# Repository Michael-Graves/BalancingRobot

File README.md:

# BalancingRobot
Repo for a balancing robot based on the TIVA C processor and Pololu's Micro Metal Gearmotors/encoders

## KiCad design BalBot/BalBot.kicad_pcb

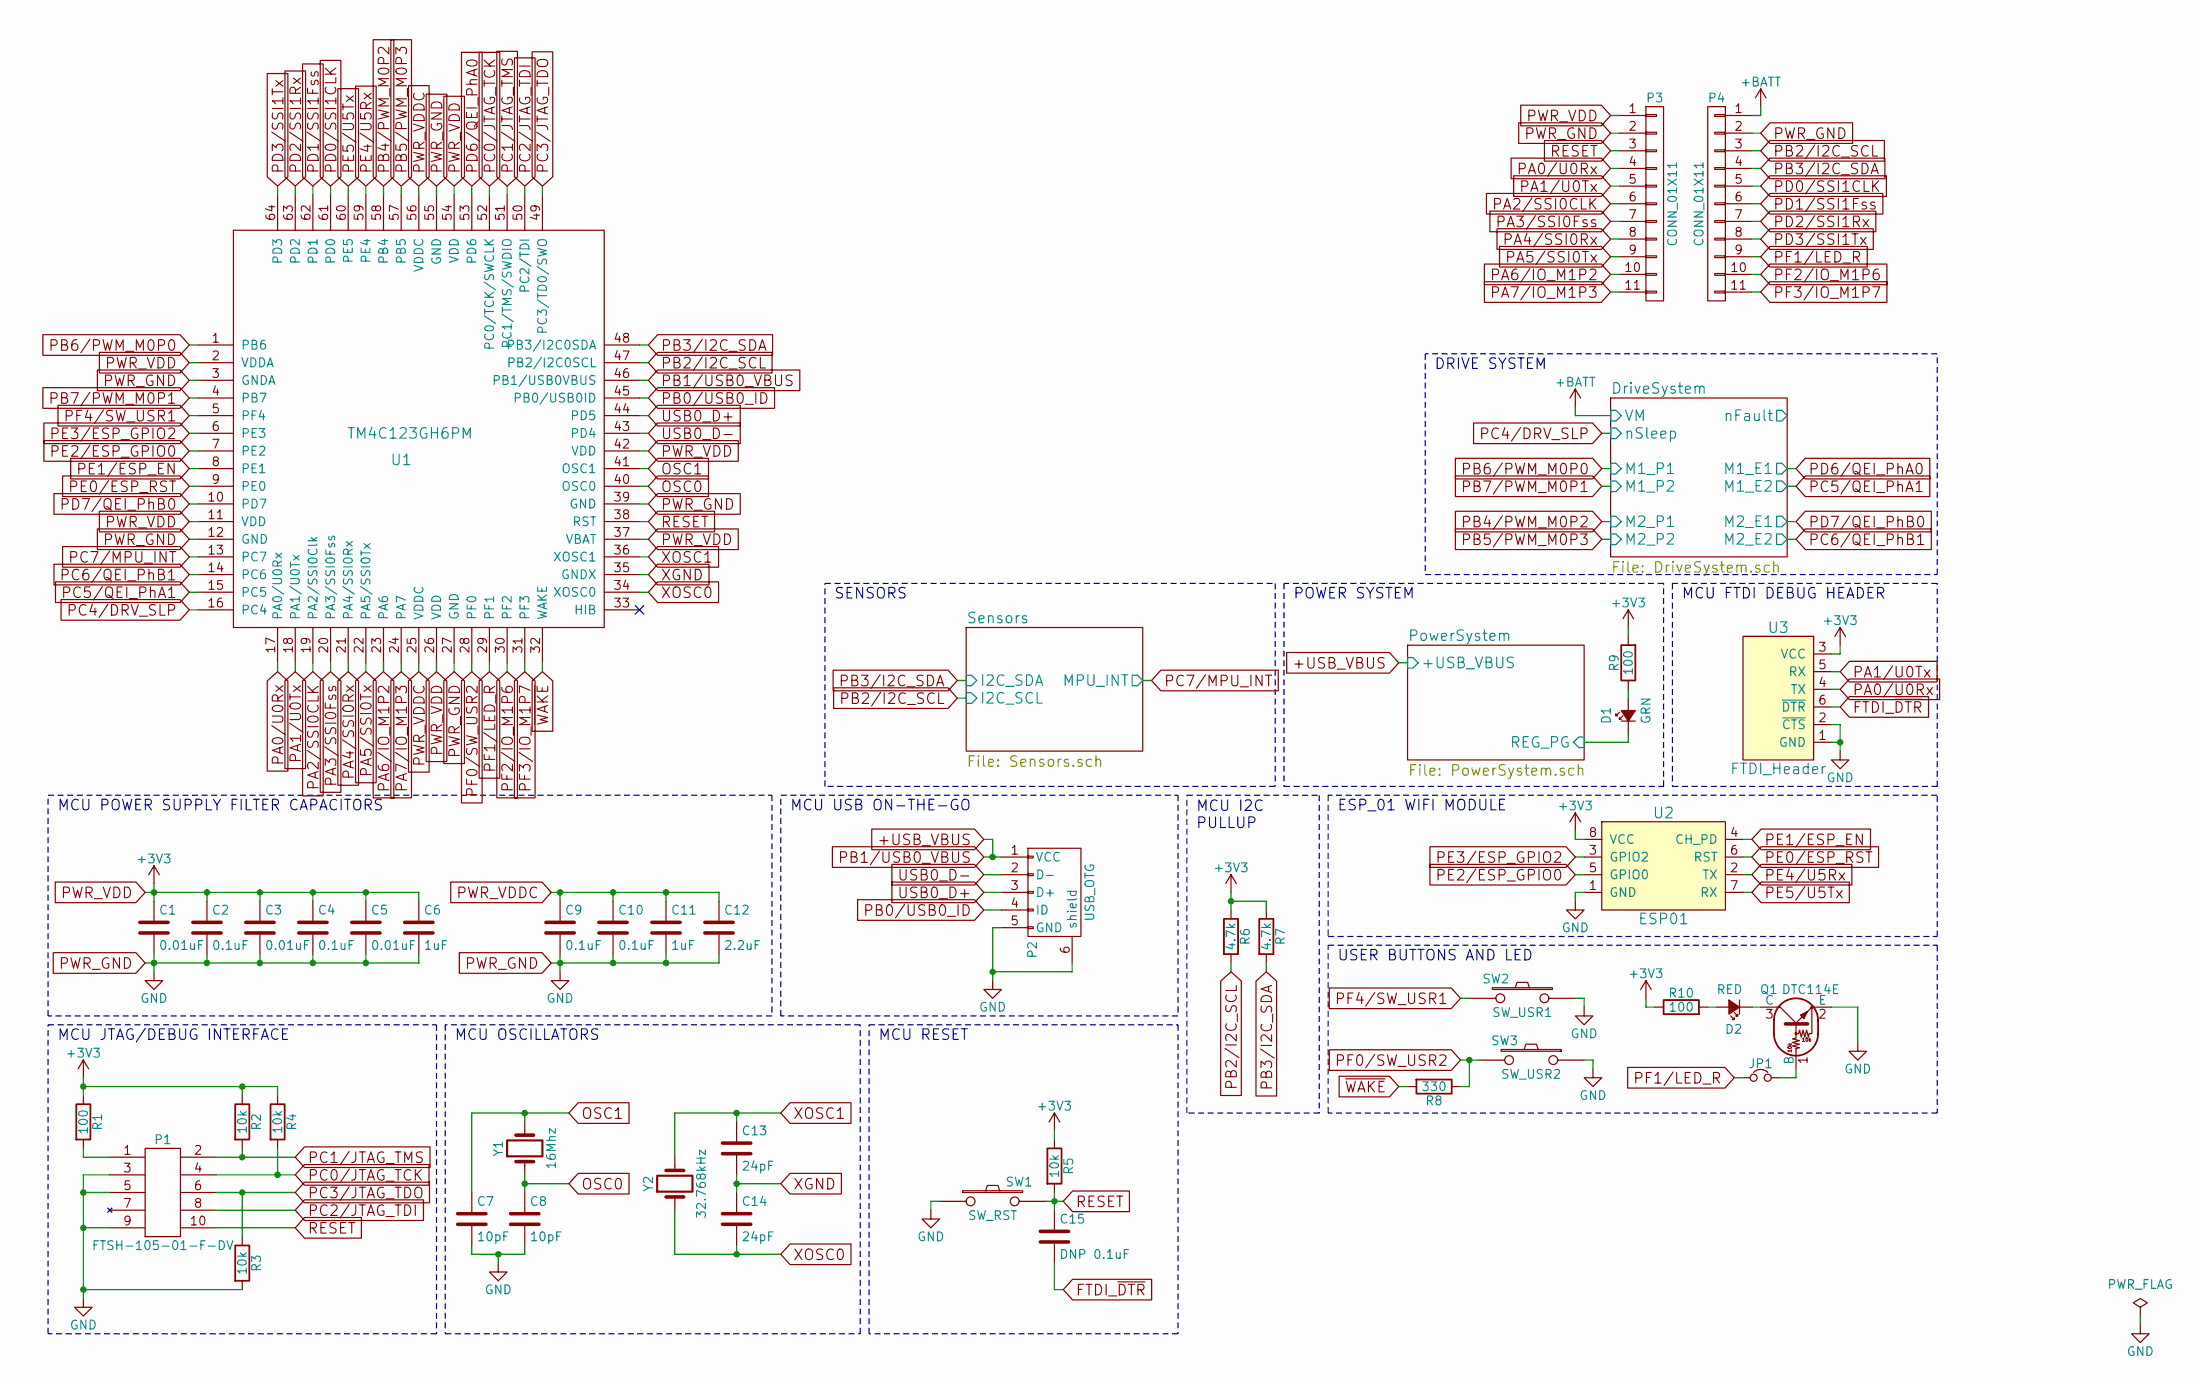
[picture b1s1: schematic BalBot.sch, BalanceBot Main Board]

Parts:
C1, C3, C5: 0.01uF; C_0402; DigiKey 490-6339-1-ND
C2, C4, C9, C10: 0.1uF; C_0402; DigiKey 490-9997-1-ND
C6, C11: 1uF; C_0402; DigiKey 490-12237-1-ND
C7, C8: 10pF; C_0402; DigiKey 490-14348-1-ND
C12: 2.2uF; C_0603; Digikey 490-3296-1-ND
C13, C14: 24pF; C_0402; DigiKey 490-17445-1-ND
C15: DNP 0.1uF; C_0402; DigiKey 490-9997-1-ND
D1: GRN; LED_0805
D2: RED; LED_0805
JP1: Jumper_NC_Small; Jumper_NC
P1: FTSH-105-01-F-DV; Pin_Header_Straight_2x05_Pitch1.00mm_SMD
P2: USB_OTG; USB_Micro-B; DigiKey 609-4618-1-ND
P3, P4: CONN_01X11; Pin_Header_Straight_1x11_Pitch2.54mm
Q1: DTC114E; SOT-416; DigiKey DTC114EET1GOSCT-ND
R1, R9, R10: 100; R_0805; DigiKey 311-100CRCT-ND
R2, R3, R4, R5: 10k; R_0805; DigiKey 311-10.0KCRCT-ND
R6, R7: 4.7k; R_0805; DigiKey 311-4.70KCRCT-ND
R8: 330; R_0805; DigiKey 311-330CRCT-ND
SW1: SW_RST; SW_SPST_6x6mm; DigiKey CKN9112CT-ND
SW2: SW_USR1; SW_SPST_6x6mm; DigiKey CKN9112CT-ND
SW3: SW_USR2; SW_SPST_6x6mm; DigiKey CKN9112CT-ND
U1: TM4C123GH6PM; LQFP-64_10x10mm_Pitch0.5mm
U2: ESP01; Pin_Header_Straight_2x04_Pitch2.54mm
U3: FTDI_Header; Pin_Header_Straight_1x06_Pitch2.54mm
Y1: 16Mhz; Crystal_SMD_5032-2pin_5.0x3.2mm; DigiKey 644-1037-1-ND
Y2: 32.768kHz; Crystal_32768Hz_Radial_Can; DigiKey 535-9033-1-ND

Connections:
+USB_VBUS: P2.1 (VCC), U1.46 (PB1/USB0VBUS); also elsewhere on the board
/PowerSystem/REG_PG: D1.1 (K); also elsewhere on the board
FTDI_~DTR: C15.2, U3.6 (~DTR)
unnamed: D1.2 (A), R9.1
unnamed: D2.1 (K), Q1.3 (C)
unnamed: D2.2 (A), R10.2
unnamed: JP1.2, Q1.1 (B)
unnamed: P1.1 (3V3), R1.2
OSC0: C8.1, U1.40 (OSC0), Y1.1
OSC1: C7.1, U1.41 (OSC1), Y1.2
PA0/U0Rx: P3.4, U1.17 (PA0/U0Rx), U3.4 (TX)
PA1/U0Tx: P3.5, U1.18 (PA1/U0Tx), U3.5 (RX)
PA2/SSI0CLK: P3.6, U1.19 (PA2/SSI0Clk)
PA3/SSI0Fss: P3.7, U1.20 (PA3/SSI0Fss)
PA4/SSI0Rx: P3.8, U1.21 (PA4/SSI0Rx)
PA5/SSI0Tx: P3.9, U1.22 (PA5/SSI0Tx)
PA6/IO_M1P2: P3.10, U1.23 (PA6)
PA7/IO_M1P3: P3.11, U1.24 (PA7)
PB0/USB0_ID: P2.4 (ID), U1.45 (PB0/USB0ID)
PB2/I2C_SCL: P4.3, R6.2, U1.47 (PB2/I2C0SCL); also elsewhere on the board
PB3/I2C_SDA: P4.4, R7.2, U1.48 (PB3/I2C0SDA); also elsewhere on the board
PB4/PWM_M0P2: U1.58 (PB4); also elsewhere on the board
PB5/PWM_M0P3: U1.57 (PB5); also elsewhere on the board
PB6/PWM_M0P0: U1.1 (PB6); also elsewhere on the board
PB7/PWM_M0P1: U1.4 (PB7); also elsewhere on the board
PC0/JTAG_TCK: P1.4 (JTAG_TCK), R4.2, U1.52 (PC0/TCK/SWCLK)
PC1/JTAG_TMS: P1.2 (JTAG_TMS), R2.2, U1.51 (PC1/TMS/SWDIO)
PC2/JTAG_TDI: P1.8 (JTAG_TDO), U1.50 (PC2/TDI)
PC3/JTAG_TDO: P1.6 (JTAG_TDO), R3.1, U1.49 (PC3/TD0/SWO)
PC4/DRV_SLP: U1.16 (PC4); also elsewhere on the board
PC5/QEI_PhA1: U1.15 (PC5); also elsewhere on the board
PC6/QEI_PhB1: U1.14 (PC6); also elsewhere on the board
PC7/MPU_INT: U1.13 (PC7); also elsewhere on the board
PD0/SSI1CLK: P4.5, U1.61 (PD0)
PD1/SSI1Fss: P4.6, U1.62 (PD1)
PD2/SSI1Rx: P4.7, U1.63 (PD2)
PD3/SSI1Tx: P4.8, U1.64 (PD3)
PD6/QEI_PhA0: U1.53 (PD6); also elsewhere on the board
PD7/QEI_PhB0: U1.10 (PD7); also elsewhere on the board
PE0/ESP_RST: U1.9 (PE0), U2.6 (RST)
PE1/ESP_EN: U1.8 (PE1), U2.4 (CH_PD)
PE2/ESP_GPIO0: U1.7 (PE2), U2.5 (GPIO0)
PE3/ESP_GPIO2: U1.6 (PE3), U2.3 (GPIO2)
PE4/U5Rx: U1.59 (PE4), U2.2 (TX)
PE5/U5Tx: U1.60 (PE5), U2.7 (RX)
PF0/SW_USR2: R8.1, SW3.2, U1.28 (PF0)
PF1/LED_R: JP1.1, P4.9, U1.29 (PF1)
PF2/IO_M1P6: P4.10, U1.30 (PF2)
PF3/IO_M1P7: P4.11, U1.31 (PF3)
PF4/SW_USR1: SW2.2, U1.5 (PF4)
PWR_GND: C1.2, C2.2, C3.2, C4.2, C5.2, C6.2, C7.2, C8.2, C9.2, C10.2, C11.2, C12.2, P1.3 (GND), P1.5 (GND), P1.9 (GND), P2.5 (GND), P2.6 (shield), P3.2, P4.2, Q1.2 (E), R3.2, SW1.1, SW2.1, SW3.1, U1.3 (GNDA), U1.12 (GND), U1.27 (GND), U1.39 (GND), U1.55 (GND), U2.1 (GND), U3.1 (GND), U3.2 (~CTS); also elsewhere on the board
PWR_VDD: C1.1, C2.1, C3.1, C4.1, C5.1, C6.1, P3.1, R1.1, R2.1, R4.1, R5.1, R6.1, R7.1, R9.2, R10.1, U1.2 (VDDA), U1.11 (VDD), U1.26 (VDD), U1.37 (VBAT), U1.42 (VDD), U1.54 (VDD), U2.8 (VCC), U3.3 (VCC); also elsewhere on the board
PWR_VDDC: C9.1, C10.1, C11.1, C12.1, U1.25 (VDDC), U1.56 (VDDC)
RESET: C15.1, P1.10 (RST_N), P3.3, R5.2, SW1.2, U1.38 (RST)
USB0_D+: P2.3 (D+), U1.44 (PD5)
USB0_D-: P2.2 (D-), U1.43 (PD4)
VIN: P4.1; also elsewhere on the board
XGND: C13.2, C14.1, U1.35 (GNDX)
XOSC0: C14.2, U1.34 (XOSC0), Y2.1
XOSC1: C13.1, U1.36 (XOSC1), Y2.2
~WAKE: R8.2, U1.32 (WAKE)

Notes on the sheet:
MCU JTAG/DEBUG INTERFACE
MCU POWER SUPPLY FILTER CAPACITORS
MCU OSCILLATORS
MCU RESET
MCU USB ON-THE-GO
MCU I2C PULLUP
USER BUTTONS AND LED
ESP_01 WIFI MODULE
POWER SYSTEM
MCU FTDI DEBUG HEADER
SENSORS
DRIVE SYSTEM

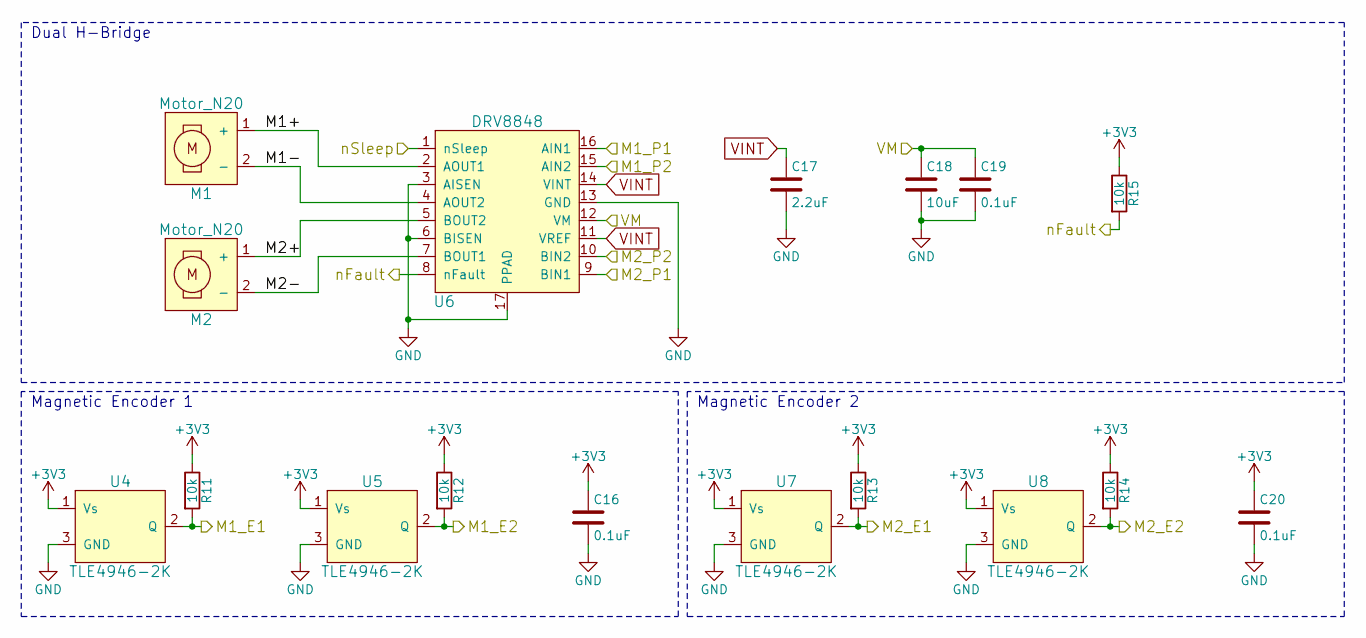
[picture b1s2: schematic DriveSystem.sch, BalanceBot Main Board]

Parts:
C16, C19, C20: 0.1uF; C_0402; DigiKey 490-9997-1-ND
C17: 2.2uF; C_0603; DigiKey 490-12235-1-ND
C18: 10uF; C_0805; DigiKey 490-12344-1-ND
M1, M2: Motor_N20
R11, R12, R13, R14, R15: 10k; R_0805; DigiKey 311-10.0KCRCT-ND
U4, U5, U7, U8: TLE4946-2K; SC-59; DigiKey TLE49462KHTSA1CT-ND
U6: DRV8848; 16-HTSSOP; DigiKey 296-38514-5-ND

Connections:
/DriveSystem/M1+: M1.1 (+), U6.2 (AOUT1)
/DriveSystem/M1-: M1.2 (-), U6.4 (AOUT2)
/DriveSystem/M2+: M2.1 (+), U6.5 (BOUT2)
/DriveSystem/M2-: M2.2 (-), U6.7 (BOUT1)
/DriveSystem/nFault: R15.2, U6.8 (nFault)
PB4/PWM_M0P2: U6.9 (BIN1); also elsewhere on the board
PB5/PWM_M0P3: U6.10 (BIN2); also elsewhere on the board
PB6/PWM_M0P0: U6.16 (AIN1); also elsewhere on the board
PB7/PWM_M0P1: U6.15 (AIN2); also elsewhere on the board
PC4/DRV_SLP: U6.1 (nSleep); also elsewhere on the board
PC5/QEI_PhA1: R12.2, U5.2 (Q); also elsewhere on the board
PC6/QEI_PhB1: R14.2, U8.2 (Q); also elsewhere on the board
PD6/QEI_PhA0: R11.2, U4.2 (Q); also elsewhere on the board
PD7/QEI_PhB0: R13.2, U7.2 (Q); also elsewhere on the board
PWR_GND: C16.2, C17.2, C18.2, C19.2, C20.2, U4.3 (GND), U5.3 (GND), U6.3 (AISEN), U6.6 (BISEN), U6.13 (GND), U6.17 (PPAD), U7.3 (GND), U8.3 (GND); also elsewhere on the board
PWR_VDD: C16.1, C20.1, R11.1, R12.1, R13.1, R14.1, R15.1, U4.1 (Vs), U5.1 (Vs), U7.1 (Vs), U8.1 (Vs); also elsewhere on the board
VIN: C18.1, C19.1, U6.12 (VM); also elsewhere on the board
VINT: C17.1, U6.11 (VREF), U6.14 (VINT)

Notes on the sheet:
Dual H-Bridge
Magnetic Encoder 1
Magnetic Encoder 2

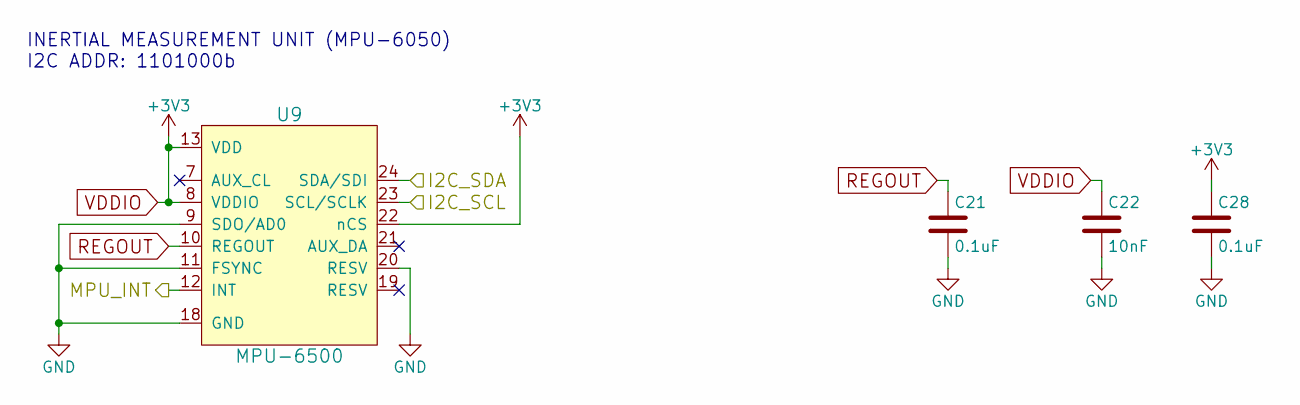
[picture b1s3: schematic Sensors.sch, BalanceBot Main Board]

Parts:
C21, C28: 0.1uF; C_0402; DigiKey 490-9997-1-ND
C22: 10nF; C_0402; DigiKey 490-16353-1-ND
U9: MPU-6500; QFN-24_3x3mm_Pitch0.4mm; DigiKey 1428-1011-1-ND

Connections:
unnamed: U9.1, U9.2, U9.3, U9.4, U9.5, U9.6, U9.14, U9.15, U9.16, U9.17
PB2/I2C_SCL: U9.23 (SCL/SCLK); also elsewhere on the board
PB3/I2C_SDA: U9.24 (SDA/SDI); also elsewhere on the board
PC7/MPU_INT: U9.12 (INT); also elsewhere on the board
PWR_GND: C21.2, C22.2, C28.2, U9.9 (SDO/AD0), U9.11 (FSYNC), U9.18 (GND), U9.20 (RESV); also elsewhere on the board
PWR_VDD: C22.1, C28.1, U9.8 (VDDIO), U9.13 (VDD), U9.22 (nCS); also elsewhere on the board
REGOUT: C21.1, U9.10 (REGOUT)

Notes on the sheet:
INERTIAL MEASUREMENT UNIT (MPU-6050) I2C ADDR: 1101000b

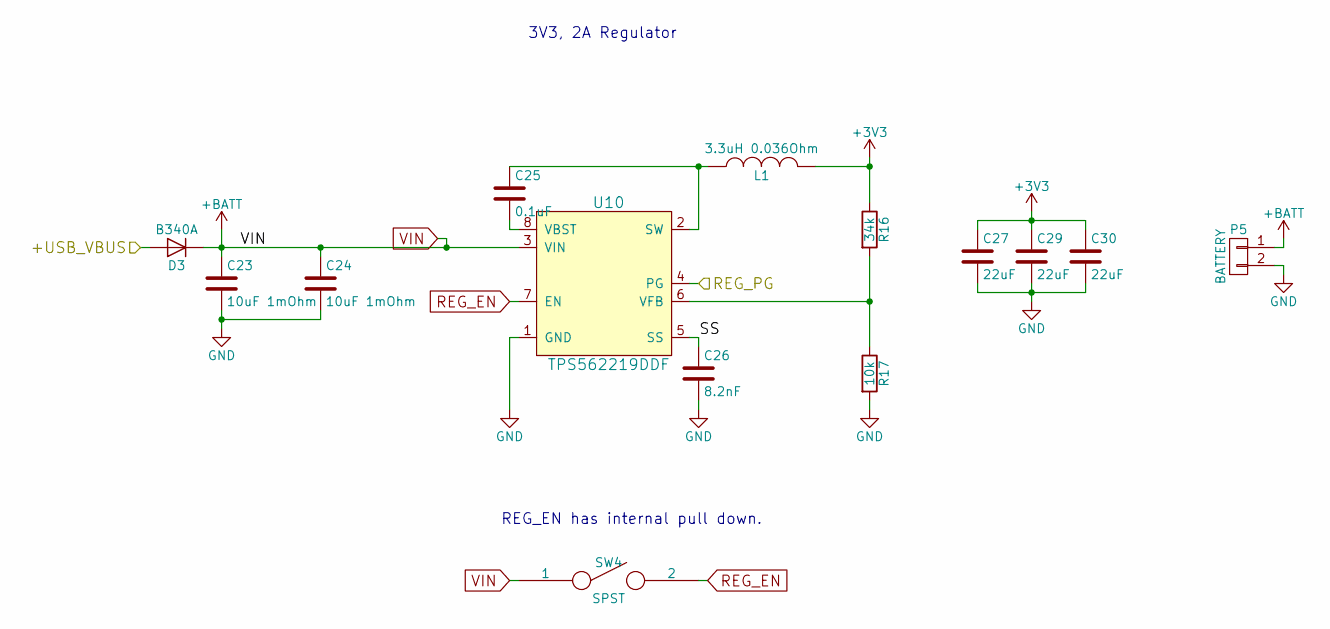
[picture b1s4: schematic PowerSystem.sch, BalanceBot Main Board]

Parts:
C23, C24: 10uF 1mOhm; C_0805; DigiKey 490-12344-1-ND
C25: 0.1uF; C_0402; DigiKey 490-9997-1-ND
C26: 8.2nF; C_0402; DigiKey 490-6338-1-ND
C27, C29, C30: 22uF; C_0603; DigiKey 1276-1193-1-ND
D3: B340A; DO-214AC
L1: 3.3uH 0.036Ohm; IND_3.3uH_ASPI-0530LR-3R3M-T2; DigiKey ASPI-0530LR-3R3M-T2CT-ND
P5: BATTERY; XT60
R16: 34k; R_0805; DigiKey 311-34.0KCRCT-ND
R17: 10k; R_0805; DigiKey 311-10.0KCRCT-ND
SW4: SPST; Pin_Header_Straight_1x02_Pitch2.54mm
U10: TPS562219DDF; SOT-23-8; DigiKey 296-48753-1-ND

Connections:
+USB_VBUS: D3.2 (A); also elsewhere on the board
/PowerSystem/REG_PG: U10.4 (PG); also elsewhere on the board
/PowerSystem/SS: C26.1, U10.5 (SS)
unnamed: C25.1, L1.1, U10.2 (SW)
unnamed: C25.2, U10.8 (VBST)
unnamed: R16.2, R17.1, U10.6 (VFB)
PWR_GND: C23.2, C24.2, C26.2, C27.2, C29.2, C30.2, P5.2, R17.2, U10.1 (GND); also elsewhere on the board
PWR_VDD: C27.1, C29.1, C30.1, L1.2, R16.1; also elsewhere on the board
REG_EN: SW4.2, U10.7 (EN)
VIN: C23.1, C24.1, D3.1 (K), P5.1, SW4.1, U10.3 (VIN); also elsewhere on the board

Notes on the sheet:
3V3, 2A Regulator
REG_EN has internal pull down.

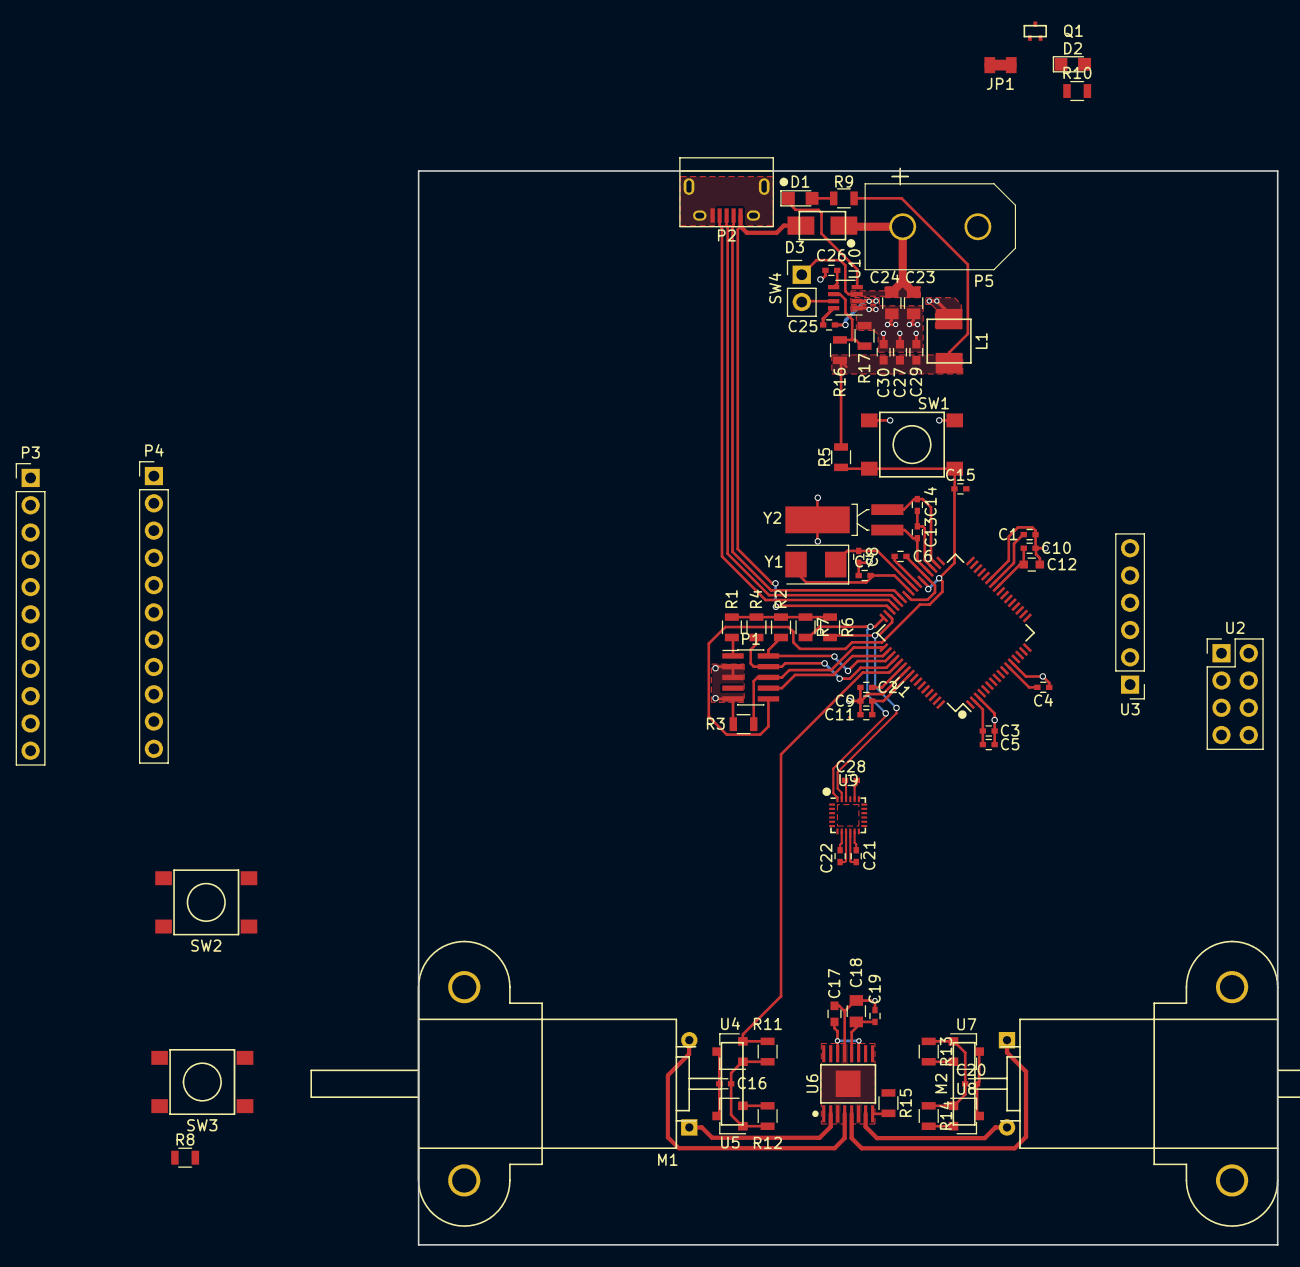
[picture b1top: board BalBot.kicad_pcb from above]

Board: 2 copper layers, 80.0 x 100.0 mm, 76 parts (0 on the bottom side), 74 nets.

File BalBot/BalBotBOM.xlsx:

BalanceBot Main Board Component Footprint Selection/BOM
Component Designation | Value 1 | Value 2 | Footprint | Digikey Part #
C1,C3,C5 | 0.01uF | 25V | 0402 | 490-6339-1-ND
C2,C4,C9,C10,C15,C16,C19,C20,C21,C28,C25 | 0.1uF | 16V | 0402 | 490-9997-1-ND
C6, C11 | 1uF | 10V | 0402 | 490-12237-1-ND
C12,C17 | 2.2uF | 16V | 0603 | 490-3296-1-ND
C7,C8 | 10pF | 50V | 0402 | 490-14348-1-ND
C13,C14 | 24pF | 50V | 0402 | 490-17445-1-ND
C18,C23,C24 | 10uF | 16V | 0805 | 490-12344-1-ND
C22 | 10nF | 16V | 0402 | 490-16353-1-ND
C26 | 8.2nF | 16V | 0402 | 490-6338-1-ND
C27,C29,C30 | 22uF | 6.3V | 0603 | 1276-1193-1-ND
D1 | GREEN |  | 0805 | 160-1423-1-ND
D2 | RED |  | 0805 | 160-1427-1-ND
D3 | B340A | 40V 3A | DO-214AC | B340A-FDICT-ND
L1 | 3.3uH | 36mOhm |  | ASPI-0530LR-3R3M-T2CT-ND
Q1 | NPN | PreBias |  | DTC114EET1GOSCT-ND
R1,R9,R10 | 100 Ohm |  | 0805 | 311-100CRCT-ND
R2,R3,R4,R5,R11,R12,R13,R14,R15,R17 | 10kOhm |  | 0805 | 311-10.0KCRCT-ND
R6,R7 | 4.7kOhm |  | 0805 | 311-4.70KCRCT-ND
R8 | 330 Ohm |  | 0805 | 311-330CRCT-ND
R16 | 34 kOhm |  | 0805 | 311-34.0KCRCT-ND
U1 | Tm4c123GH6PM |  | LQFP-64_10x10mm | 296-46360-1-ND
U2 | ESP01_Header |  | Header_2x4
U3 | FTDI_Header |  | Header_1x6
U4,U5,U7,U8 | TLE4946-2K | Encoder | SC-59 | TLE49462KHTSA1CT-ND
U6 | DRV8848 | Motor Driver | 16-HTSSOP | 296-38514-5-ND
U9 | MPU-6500 | 6DOF IMU | 24QFN | 1428-1011-1-ND
U10 | TPS562219DDF | 3V3 SMPS | SOT23-8 | 296-48753-1-ND
Y1 | 16Mhz | Crystal | 2-SMD | 644-1037-1-ND
Y2 | 32.768kHz | Crystal | Cylindrical Can | 535-9033-1-ND
P2 | USB microB | Surface,Right-Angle,ThroughHole |  | 609-4618-1-ND

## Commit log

2018-05-06 First Commit, schematic pretty much finished, started assigning footprints/digikey components
2018-05-07 Started layout
2018-05-08 Working On Layout
